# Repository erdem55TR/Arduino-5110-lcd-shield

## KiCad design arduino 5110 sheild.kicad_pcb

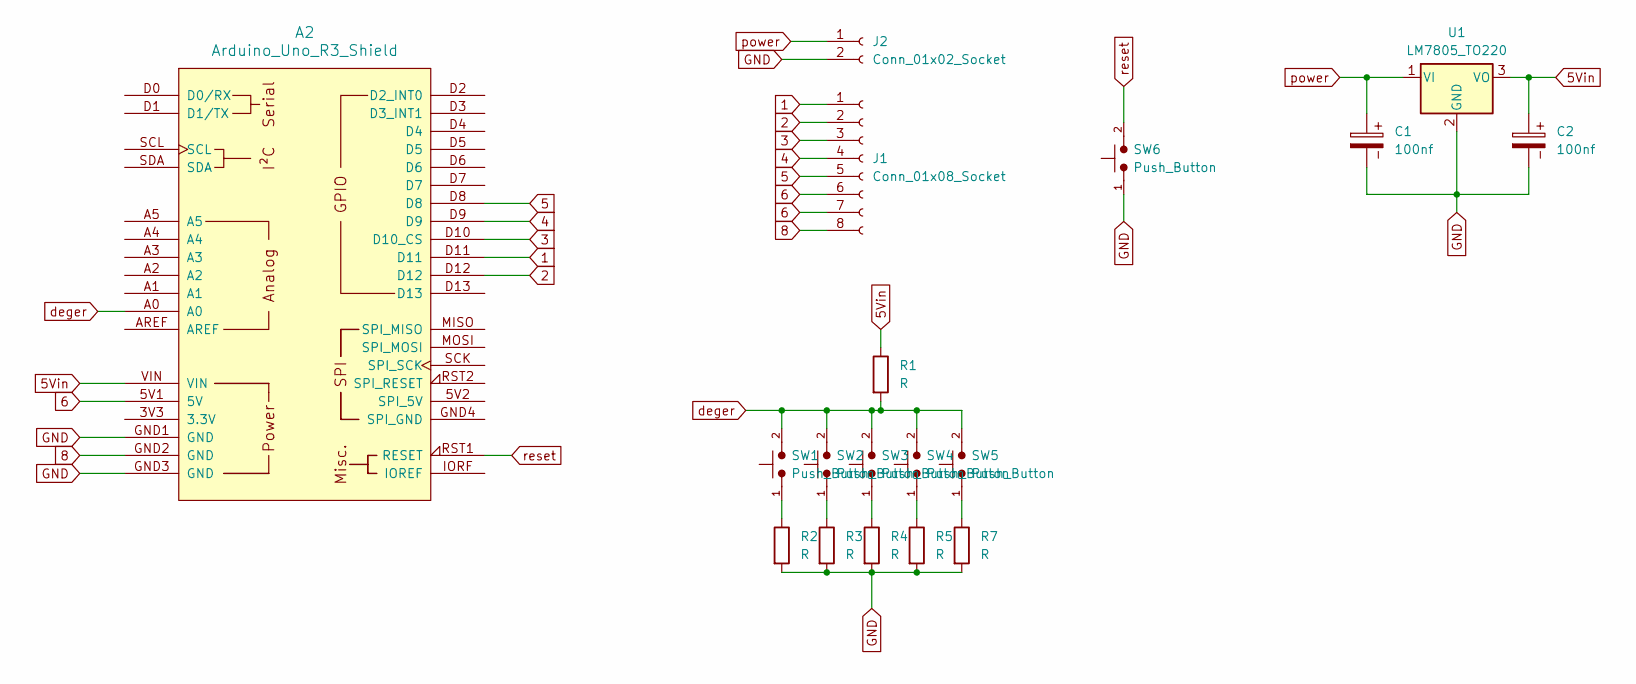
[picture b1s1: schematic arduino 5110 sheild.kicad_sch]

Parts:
A2: Arduino_Uno_R3_Shield
C1, C2: 100nf; C_Rect_L7.0mm_W4.5mm_P5.00mm
J1: Conn_01x08_Socket; PinHeader_1x08_P2.54mm_Vertical
J2: Conn_01x02_Socket; PhoenixContact_MCV_1,5_2-G-5.08_1x02_P5.08mm_Vertical
R1, R2, R3, R4, R5, R7: R; R_Axial_DIN0204_L3.6mm_D1.6mm_P5.08mm_Horizontal
SW1, SW2, SW3, SW4, SW5, SW6: Push_Button; SW_PUSH_6mm
U1: LM7805_TO220; TO-220-3_Vertical

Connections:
1: A2.D11, J1.1
2: A2.D12, J1.2
3: A2.D10 (D10_CS), J1.3
4: A2.D9, J1.4
5: A2.D8, J1.5
5Vin: A2.VIN, C2.1, R1.1, U1.3 (VO)
6: A2.5V1 (5V), J1.6, J1.7
8: A2.GND2 (GND), J1.8
GND: A2.GND1 (GND), A2.GND3 (GND), C1.2, C2.2, J2.2, R2.2, R3.2, R4.2, R5.2, R7.2, SW6.1, U1.2 (GND)
unnamed: R2.1, SW1.1
unnamed: R3.1, SW2.1
unnamed: R4.1, SW3.1
unnamed: R5.1, SW4.1
unnamed: R7.1, SW5.1
deger: A2.A0, R1.2, SW1.2, SW2.2, SW3.2, SW4.2, SW5.2
power: C1.1, J2.1, U1.1 (VI)
reset: A2.RST1 (RESET), SW6.2

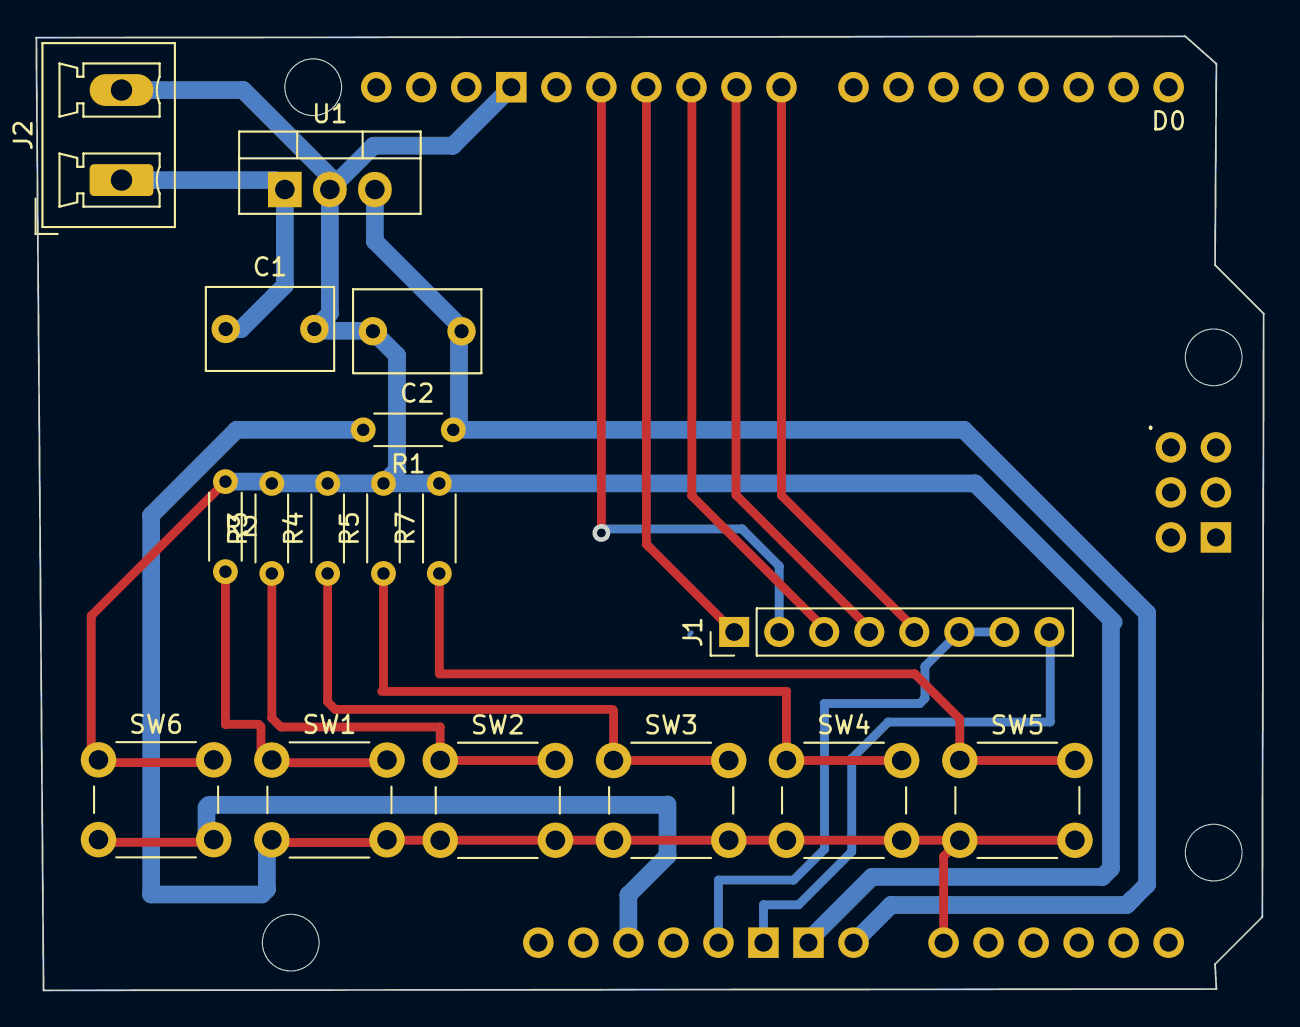
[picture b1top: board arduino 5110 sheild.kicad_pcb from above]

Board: 2 copper layers, 69.2 x 53.8 mm, 18 parts (0 on the bottom side), 17 nets.
